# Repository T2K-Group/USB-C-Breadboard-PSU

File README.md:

# USB-C Breadboard Power Supply

Introducing a sleek USB-C breadboard power supply designed to modernize and streamline your electronics projects. Say goodbye to the cumbersome 9V batteries and DC barrel jacks. This board brings convenience and efficiency to your workbench.

## Key Features:

- Dual Voltage Output: Easily select between 5V and 3.3V outputs to accommodate a variety of components and circuits.
- Breadboard-Friendly Design: Perfectly fits a 840-pin breadboard, enabling a secure and stable connection.
- Independent Side Outputs: Manage different voltage needs on each side of your breadboard with independent switchable outputs.

## Ordering infomation

All Production files can be found in the `Production` folder. The Gerber files are named `usbcpower.zip` and the bill of materials is named `bom.csv`. The board is designed to be manufactured with 1.6mm FR4 and ENIG finish. The board is designed to be assembled with 0805 SMD components.

The BOM cost for this project is approximately £7.80 [see Digikey List](https://www.digikey.co.uk/en/mylists/list/3C8NIB07NC), It is possible to reduce this cost by using parts from other suppliers (LCSC etc.)

> Please inspect your boards for quality and always test your boards before use. If you have any issues with the boards, please contact us at `opensource at t2k dot group`.

## Enhance Your Projects

Our USB-C power supply is not just compact and user-friendly, but also a step towards modernising your electronic designs. Its easy-to-use interface is designed for hobbyists and professionals alike, making it a must-have tool for any electronics kit.
Open Source Commitment

## Designed for Beginners and Professionals

All components are 0805 SMD with hand soldering pads, This makes it possible to assemble the devices at home with a soldering iron and a steady hand. The board is designed to be easy to assemble and use, making it a great learning tool for beginners and a convenient tool for professionals.

## Open Source Commitment

While this project is proudly open source, please note that the "T2K Group" logo on the PCB is a copyright of T2K Group Limited and must remain unaltered. However, you are free to remove it from the board completely if you wish to do so.

This board was designed by [J.Fitton](https://github.com/jackfitton112/) for T2K Group Limited. If you have any questions or feedback, please feel free to reach out to us at `opensource at t2k dot group`.

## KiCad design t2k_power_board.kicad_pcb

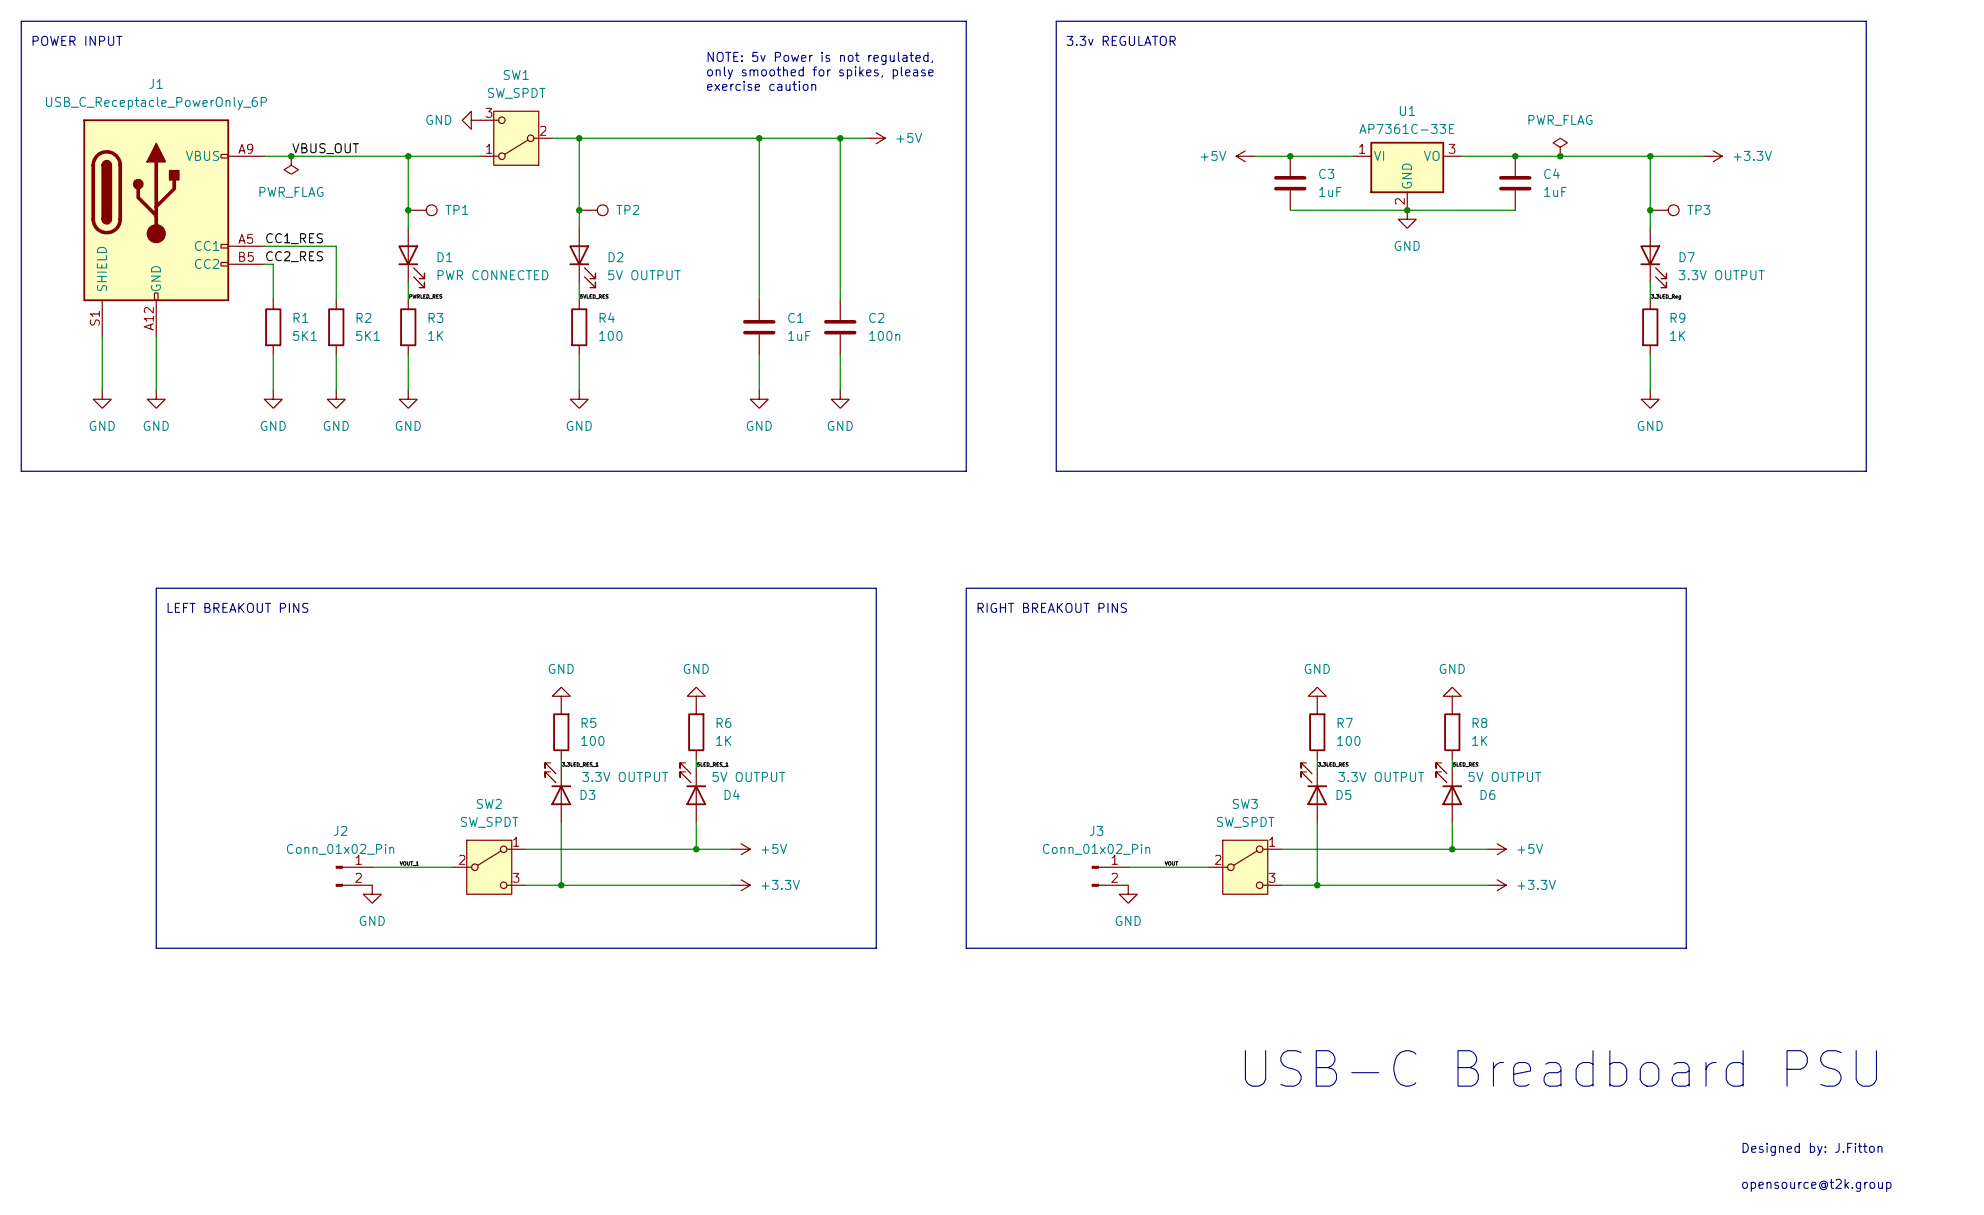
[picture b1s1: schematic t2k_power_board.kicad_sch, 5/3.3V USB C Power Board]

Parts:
C1, C3, C4: 1uF; C_0805_2012Metric_Pad1.18x1.45mm_HandSolder
C2: 100n; C_0805_2012Metric_Pad1.18x1.45mm_HandSolder
D1: PWR CONNECTED; LED_0805_2012Metric_Pad1.15x1.40mm_HandSolder
D2, D4, D6: 5V OUTPUT; LED_0805_2012Metric_Pad1.15x1.40mm_HandSolder
D3, D5, D7: 3.3V OUTPUT; LED_0805_2012Metric_Pad1.15x1.40mm_HandSolder
J1: USB_C_Receptacle_PowerOnly_6P; USB_C_Receptacle_GCT_USB4135-GF-A_6P_TopMnt_Horizontal
J2, J3: Conn_01x02_Pin; PinHeader_1x02_P2.54mm_Vertical
R1, R2: 5K1; R_0805_2012Metric_Pad1.20x1.40mm_HandSolder
R3, R6, R8, R9: 1K; R_0805_2012Metric_Pad1.20x1.40mm_HandSolder
R4, R5, R7: 100; R_0805_2012Metric_Pad1.20x1.40mm_HandSolder
SW1, SW2, SW3: SW_SPDT; SW_SPDT_PCM12
TP1, TP2, TP3: TestPoint; TestPoint_Pad_D1.0mm
U1: AP7361C-33E; SOT-223-3_TabPin2

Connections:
+3.3V: C4.1, D3.2 (A), D5.2 (A), D7.2 (A), SW2.3 (C), SW3.3 (C), TP3.1, U1.3 (VO)
+5V: C1.1, C2.1, C3.1, D2.2 (A), D4.2 (A), D6.2 (A), SW1.2 (B), SW2.1 (A), SW3.1 (A), TP2.1, U1.1 (VI)
/3.3LED_RES: D5.1 (K), R7.1
/3.3LED_RES_1: D3.1 (K), R5.1
/3.3LED_Reg: D7.1 (K), R9.1
/5LED_RES: D6.1 (K), R8.1
/5LED_RES_1: D4.1 (K), R6.1
/5VLED_RES: D2.1 (K), R4.1
/CC1_RES: J1.A5 (CC1), R2.1
/CC2_RES: J1.B5 (CC2), R1.1
/PWRLED_RES: D1.1 (K), R3.1
/VBUS_OUT: D1.2 (A), J1.A9 (VBUS), J1.B9 (VBUS), SW1.1 (A), TP1.1
/VOUT: J3.1, SW3.2 (B)
/VOUT_1: J2.1, SW2.2 (B)
GND: C1.2, C2.2, C3.2, C4.2, J1.A12 (GND), J1.B12 (GND), J1.S1 (SHIELD), J2.2, J3.2, R1.2, R2.2, R3.2, R4.2, R5.2, R6.2, R7.2, R8.2, R9.2, SW1.3 (C), U1.2 (GND)

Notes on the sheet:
USB-C Breadboard PSU
POWER INPUT
RIGHT BREAKOUT PINS
LEFT BREAKOUT PINS
Designed by: J.Fitton
NOTE: 5v Power is not regulated, only smoothed for spikes, please exercise caution
opensource@t2k.group
3.3v REGULATOR

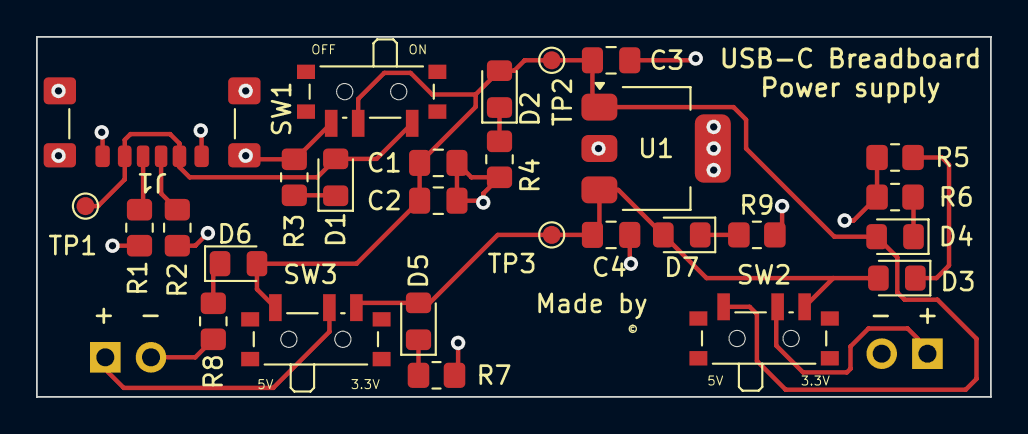
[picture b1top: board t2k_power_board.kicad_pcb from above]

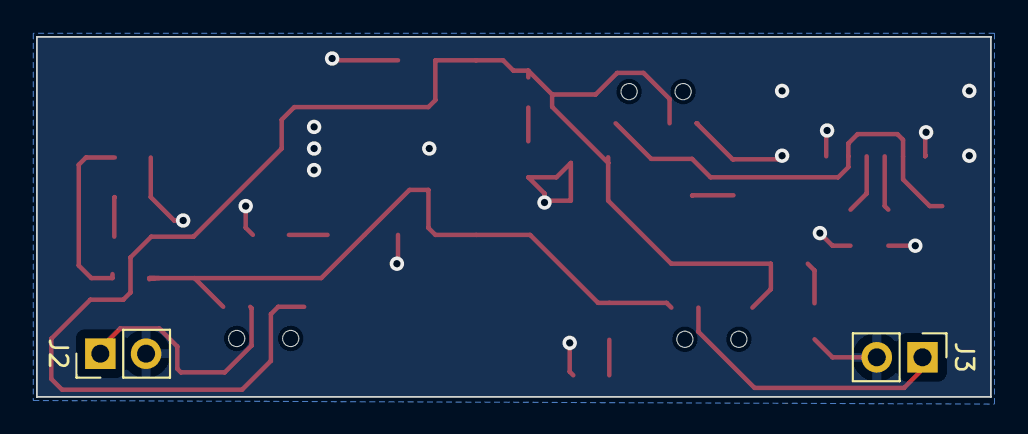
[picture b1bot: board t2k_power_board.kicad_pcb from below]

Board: 2 copper layers, 53.0 x 20.0 mm, 30 parts (2 on the bottom side), 15 nets.

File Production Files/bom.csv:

Designator,Footprint,Quantity,Part,Part Number
"C1, C3, C4",0805,3,1uF,CL21B105KAFNNNE
C2,0805,1,100n,CC0805KRX7R9BB104
"D1, D2, D3, D4, D5, D6, D7",0805,7,LED,5988170107F,
J1,USB_C_Receptacle_6P,1,USBC,USB4135-GF-A,
"J2, J3",PinHeader_1x02_P2.54mm_Vertical,2,Conn_01x02_Pin,TS-102-G-A-1,
"R1, R2",0805,2,5K1,RC0805JR-075K1L
"R3, R6, R8, R9",0805,4,1K,RC0805FR-071KL
"R4, R5, R7",0805,3,100,RC0805FR-0710KL
"SW1, SW2, SW3",SW_SPDT_PCM12,3,SW_SPDT,PCM12SMTR
"TP1, TP2, TP3",TestPoint_Pad_D1.0mm,3,TestPoint,NC
U1,SOT-223-3_TabPin2,1,AP7361C-33E,AP7361C-33ER-13
